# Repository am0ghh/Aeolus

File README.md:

# Aeolus

**Aeolus** is a smart, temperature-aware IR fan controller built around an ESP32-C3. It watches room temperature and automatically turns a WOOZOO (or other NEC-protocol) fan on and off over infrared, with a 0.96" OLED status display, a physical control button, and an on-device IR "learn" mode for capturing new remote codes — all on a custom-designed 4-layer PCB.

Named after Aeolus, the keeper of the winds.

## Gallery

**3D render**

**PCB layout** (4-layer, black soldermask, silkscreen branding)

**Schematic**

## Background — this is v2 of my [fans](https://github.com/am0ghh/fans) project

Aeolus is a ground-up redesign of my earlier [dorm-room fan automation project](https://github.com/am0ghh/fans). The original ("fans") was an Arduino Uno R3 on a breadboard: a DHT11 sensor, an IR receiver, and a transistor-driven IR LED that automatically toggled the fan on hysteresis. It worked, but it was bulky, code-only, and limited to hardcoded remote codes.

Aeolus keeps the proven control logic and rebuilds everything around it as a real, compact, hardware product.

### Design improvements over v1 (`fans`)

| Area | v1 — `fans` | v2 — Aeolus |
|------|-------------|-------------|
| **Microcontroller** | Arduino Uno R3 (ATmega328P, 5V, large) | ESP32-C3 SuperMini (32-bit RISC-V, 3.3V, tiny, Wi-Fi/BLE capable) |
| **Temperature sensing** | DHT11 module (slow, ~1 Hz, NaN dropouts) | NTC thermistor read on the ADC with a Beta-equation conversion — faster, cheaper, no library timing quirks |
| **Display** | None (serial monitor only) | 0.96" SSD1306 I²C OLED with live temp/state readout and wind/snow animations |
| **User input** | None | Physical push button — single/double-tap for mode and manual control |
| **Remote codes** | Hardcoded in firmware | On-device IR **learn/scan mode** — capture a new remote's code without reflashing |
| **Build** | Breadboard / protoboard prototype | Custom 4-layer PCB designed in KiCad (SIG–GND–PWR–SIG stackup), black soldermask, silkscreen branding |
| **Form factor** | Loose modules and jumper wires | Single integrated board with the OLED and modules socketed |

The transistor-buffered IR transmitter (the key range fix from v1 — extends usable range from a couple of inches to ~10–15 ft) is carried over into the Aeolus hardware.

## Hardware

- **ESP32-C3 SuperMini** microcontroller module
- **0.96" SSD1306 OLED** (I²C, address `0x3C`)
- **NTC thermistor** on the ADC for temperature sensing
- **IR receiver** (38 kHz demodulating, VS1838B-style) for learning remote codes
- **IR LED (940 nm)** transmitter, transistor-buffered for range
- **Momentary push button** for manual control / mode switching
- Custom 4-layer KiCad PCB (`hardware/Aeolus.kicad_pcb` / `.kicad_sch`)

### Pin map

| Function | ESP32-C3 GPIO |
|----------|---------------|
| IR transmit | GPIO5 |
| IR receive | GPIO3 |
| OLED SDA | GPIO7 |
| OLED SCL | GPIO6 |
| Button | GPIO10 |
| Thermistor (ADC) | GPIO0 |

## Firmware

The firmware lives in [`src/main.cpp`](src/main.cpp) and is built with PlatformIO (Arduino framework for ESP32-C3).

- **Automatic control with hysteresis** — fan turns on at 75 °F, off at 73 °F, so it won't rapidly cycle around the setpoint.
- **Minimum run time** — once the fan starts, it stays on for at least 10 minutes.
- **Two operating modes** — a normal run/monitor mode and a scan (IR-learn) mode, toggled from the button.
- **IR learn mode** — point your fan remote at the receiver and Aeolus captures the raw NEC code so it can replay it later.
- **OLED UI** — shows current temperature and fan state with animated wind (fan on) and snow (idle/cool) effects.
- Sends NEC-protocol IR commands (default is the WOOZOO fan power code).

### Build & flash

This is a [PlatformIO](https://platformio.org/) project:

```bash
pio run              # build
pio run -t upload    # flash to the ESP32-C3
pio device monitor   # serial output
```

Board and framework are configured in [`platformio.ini`](platformio.ini). Libraries used: IRremote, Adafruit SSD1306, Adafruit GFX.

## PCB & hardware design

The KiCad 9 project is in [`hardware/`](hardware/) (schematic, PCB, custom symbol/footprint libraries). Highlights:

- **4-layer board** — SIG–GND–PWR–SIG. `In1.Cu` carries a poured GND plane and `In2.Cu` a poured +3.3V plane. Every ground and supply pad is through-hole, so the plated barrels tie straight into the planes with thermal reliefs and no stitching vias are needed. That is why there is not a single GND trace on `F.Cu` — the plane carries every return, which keeps the loop area of the switched IR LED current away from the high-impedance thermistor sense line.
- **Custom ESP32-C3 SuperMini symbol and footprint**, pin-labeled to match the actual module.
- **Custom silkscreen branding** (the "Aeolus" wordmark) generated from the artwork in [`branding/`](branding/).
- 3D models for the ESP32-C3, OLED, and IR components in `hardware/Aeolus.3dshapes/` for a complete 3D render.

## Known limitations

Stated up front so the files and the description agree:

- **Signal routing is single-sided.** All 75 copper segments sit on `F.Cu`; `B.Cu` is unused for routing. This is fine at this node count because power and ground are handled by the inner planes rather than by surface traces.
- **No decoupling capacitors are placed.** `schematic-guide.txt` calls for 100 nF on the OLED and IR receiver supplies; those parts are not yet in the schematic.
- **No I²C pull-ups on the board** — the design relies on the ones fitted to the OLED breakout.
- **The board has not been fabricated.** Everything in `hardware/` is layout and 3D render only; no gerbers, BOM, or assembled unit yet.
- **The IR range figures are estimates**, not instrumented measurements.

## License

See [LICENSE](LICENSE).

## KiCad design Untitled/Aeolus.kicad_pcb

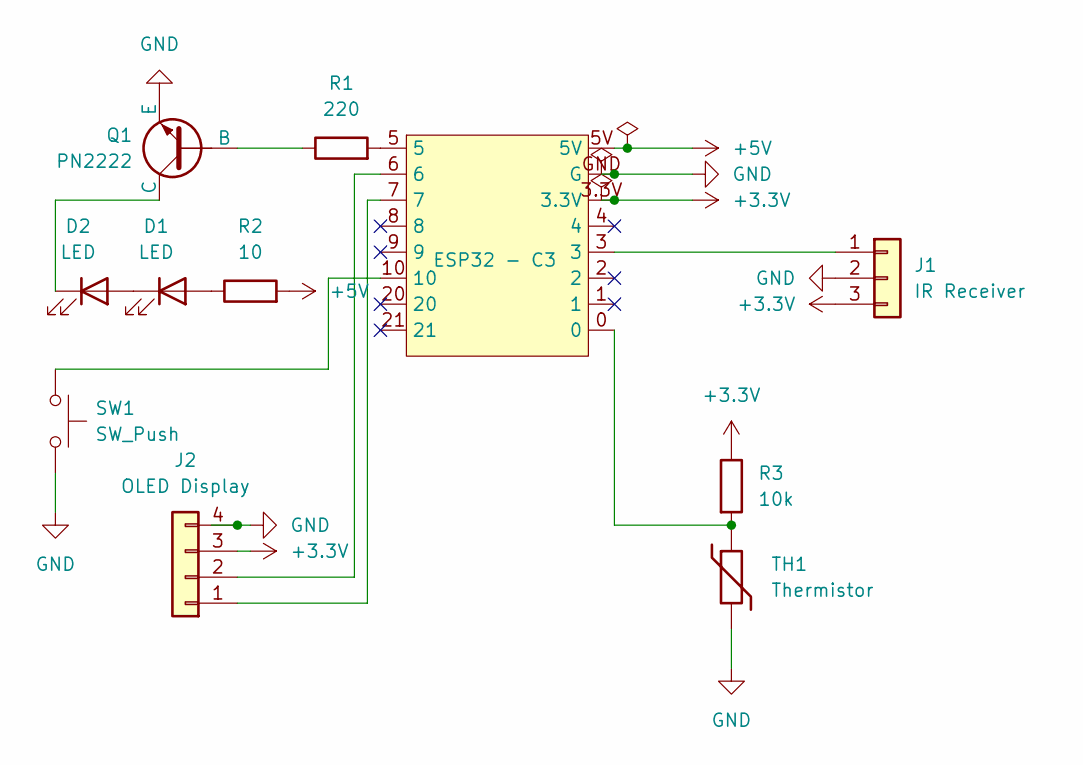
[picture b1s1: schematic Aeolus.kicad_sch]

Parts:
D1, D2: LED; LED_PLCC-2_3.4x3.0mm_KA
J1: IR Receiver; Vishay_MINICAST-3Pin
J2: OLED Display; OLED_SSD1306_I2C_0.96
Q1: PN2222; TO-92
R1: 220; R_0805_2012Metric
R2: 10; R_2512_6332Metric
R3: 10k; R_0805_2012Metric
SW1: SW_Push; SW_PUSH_6mm
TH1: Thermistor; C_Disc_D3.0mm_W1.6mm_P2.50mm
U1: ESP32 - C3; ESP32-C3-SuperMini

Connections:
+3.3V: J1.3, J2.3, R3.1, U1.3.3V
+5V: R2.2, U1.5V
GND: J1.2, J2.4, Q1.3 (E), SW1.2, TH1.2, U1.GND (G)
unnamed: D1.2 (A), R2.1
unnamed: D1.1 (K), D2.2 (A)
unnamed: D2.1 (K), Q1.1 (C)
unnamed: J1.1, U1.3
unnamed: J2.1, U1.7
unnamed: J2.2, U1.6
unnamed: Q1.2 (B), R1.1
unnamed: R1.2, U1.5
unnamed: R3.2, TH1.1, U1.0
unnamed: SW1.1, U1.10

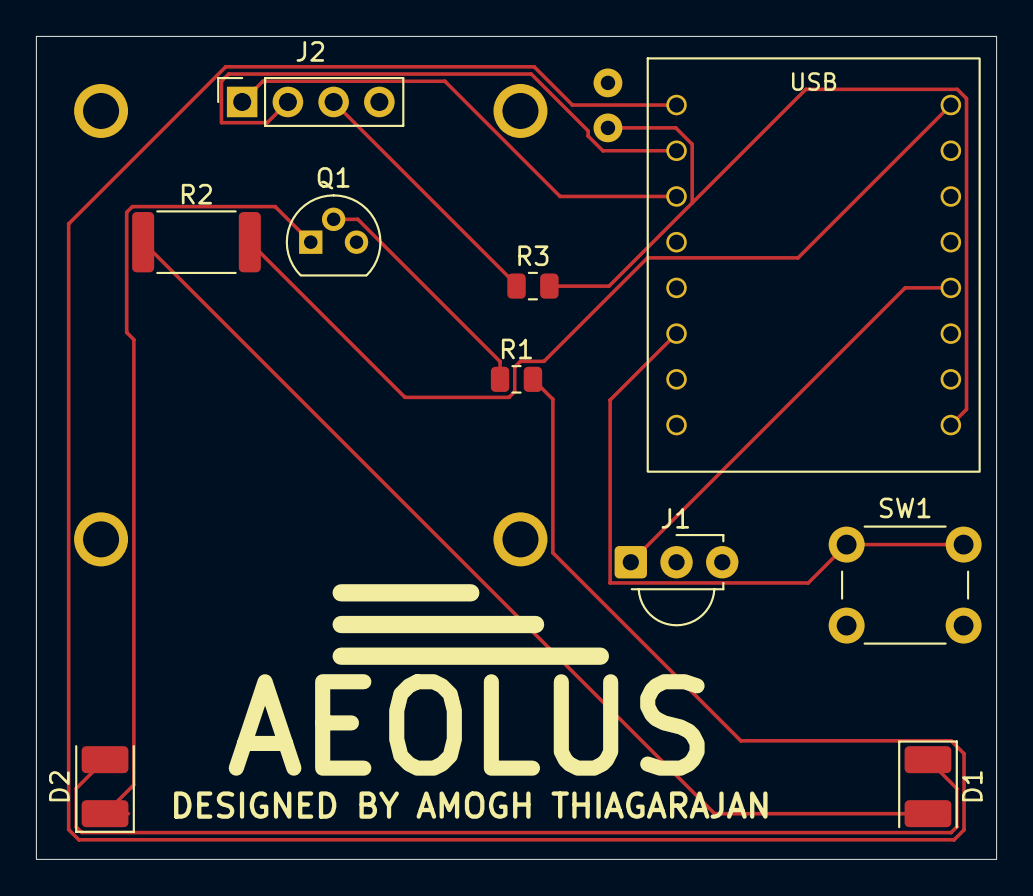
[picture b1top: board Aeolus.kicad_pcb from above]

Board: 4 copper layers, 53.3 x 45.7 mm, 11 parts (1 on the bottom side), 13 nets.
